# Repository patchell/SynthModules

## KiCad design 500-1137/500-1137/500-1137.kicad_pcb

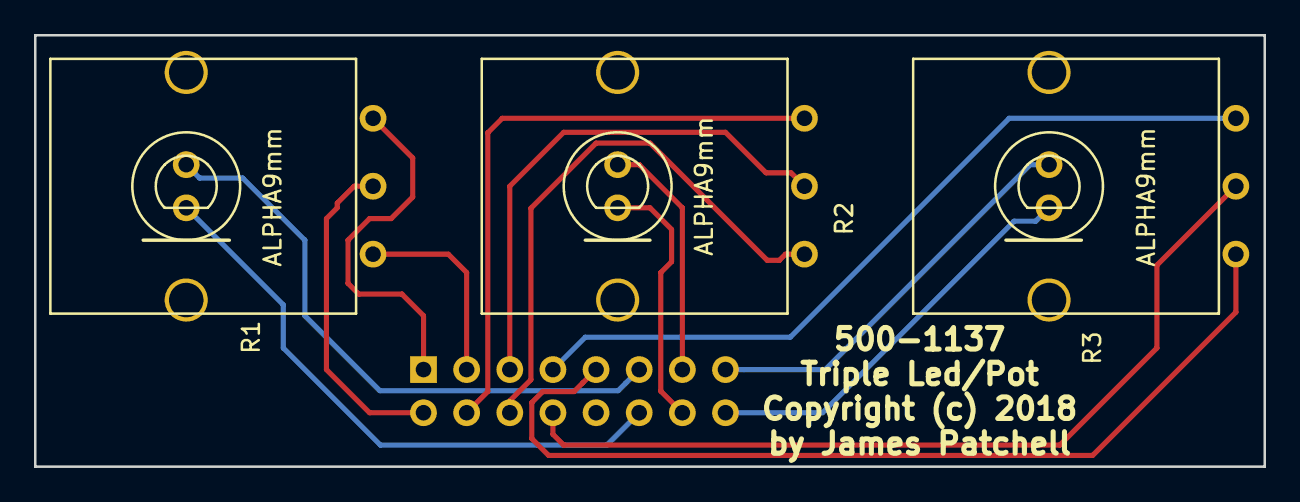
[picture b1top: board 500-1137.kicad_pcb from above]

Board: 2 copper layers, 72.4 x 25.4 mm, 4 parts (1 on the bottom side), 15 nets.

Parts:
P1: 500-1137; IDC8x2_Vert
R1, R2, R3: ALPHA9mm; Alpha9mmPotWithLED

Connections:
unnamed: P1.1, R1.3
unnamed: P1.2, R1.2
unnamed: P1.3, R1.1
unnamed: P1.4, R2.3
unnamed: P1.5, R2.2
unnamed: P1.6, R2.1
unnamed: P1.7, R3.3
unnamed: P1.8, R3.2
unnamed: P1.9, R3.1
unnamed: P1.11, R1.5
unnamed: P1.12, R1.4
unnamed: P1.13, R2.5
unnamed: P1.14, R2.4
unnamed: P1.15, R3.5
unnamed: P1.16, R3.4

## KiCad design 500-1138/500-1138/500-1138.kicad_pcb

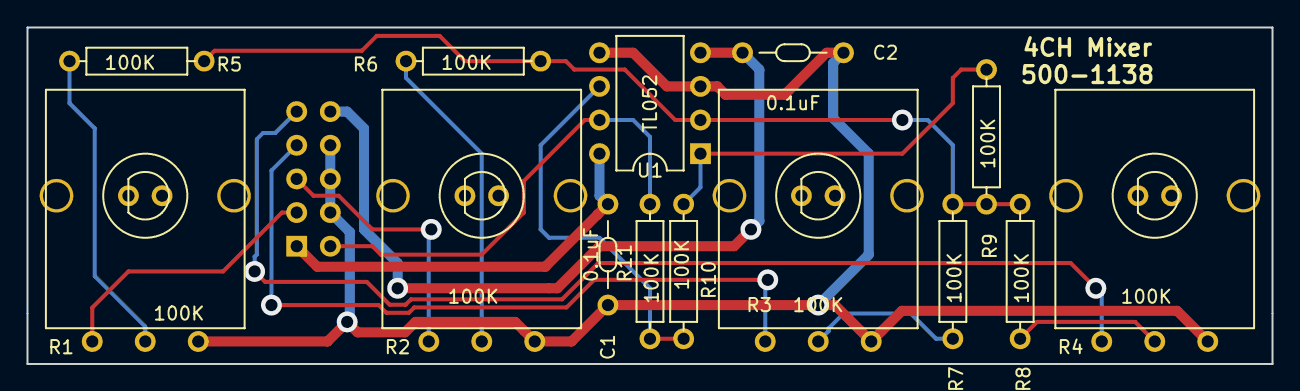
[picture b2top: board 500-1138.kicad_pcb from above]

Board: 2 copper layers, 94.0 x 25.4 mm, 15 parts (1 on the bottom side), 15 nets.

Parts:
C1, C2: 0.1uF; CAP-Bypass-0.3
P1: 500-1138; IDC5x2_Vert
R1, R2, R3, R4: 100K; Alpha9mmPotWithLED
R5, R6, R7, R8, R9, R10, R11: 100K; AXIAL0.4
U1: TL052; DIP8.3

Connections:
/V+: C1.1, P1.1, U1.8
/V-: C2.1, P1.10, U1.4
GND: C1.2, C2.2, P1.4, P1.6, P1.8, R1.3, R2.3, R3.3, R4.3, U1.3, U1.5
unnamed: P1.2, R11.2, U1.7
unnamed: P1.3, R1.1
unnamed: P1.5, R2.1
unnamed: P1.7, R3.1
unnamed: P1.9, R4.1
unnamed: R1.2, R5.1
unnamed: R2.2, R6.1
unnamed: R3.2, R7.1
unnamed: R4.2, R8.1
unnamed: R5.2, R6.2, R7.2, R8.2, R9.1, U1.2
unnamed: R9.2, R10.1, U1.1
unnamed: R10.2, R11.1, U1.6

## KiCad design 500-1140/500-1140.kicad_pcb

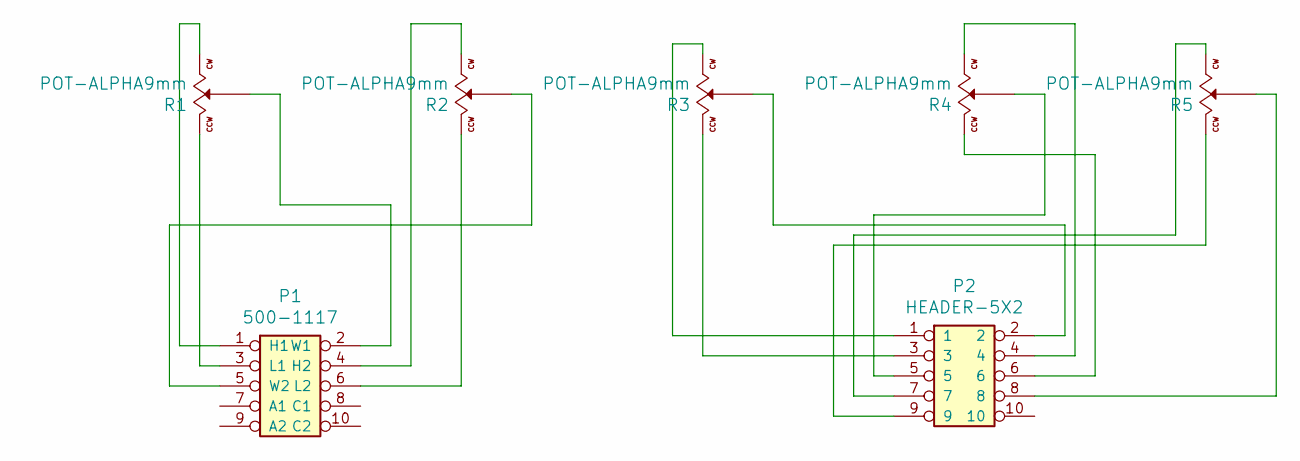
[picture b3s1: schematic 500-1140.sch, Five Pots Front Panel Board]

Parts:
P1: 500-1117; IDC5x2_Vert
P2: HEADER-5X2; IDC5x2_Vert
R1, R2, R3, R4, R5: POT-ALPHA9mm; Alpha_9mm_Pot

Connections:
unnamed: P1.1 (H1), R1.3 (B)
unnamed: P1.2 (W1), R1.2 (Wiper)
unnamed: P1.3 (L1), R1.1 (A)
unnamed: P1.4 (H2), R2.3 (B)
unnamed: P1.5 (W2), R2.2 (Wiper)
unnamed: P1.6 (L2), R2.1 (A)
unnamed: P2.1, R3.3 (B)
unnamed: P2.2, R3.2 (Wiper)
unnamed: P2.3, R3.1 (A)
unnamed: P2.4, R4.3 (B)
unnamed: P2.5, R4.2 (Wiper)
unnamed: P2.6, R4.1 (A)
unnamed: P2.7, R5.3 (B)
unnamed: P2.8, R5.2 (Wiper)
unnamed: P2.9, R5.1 (A)

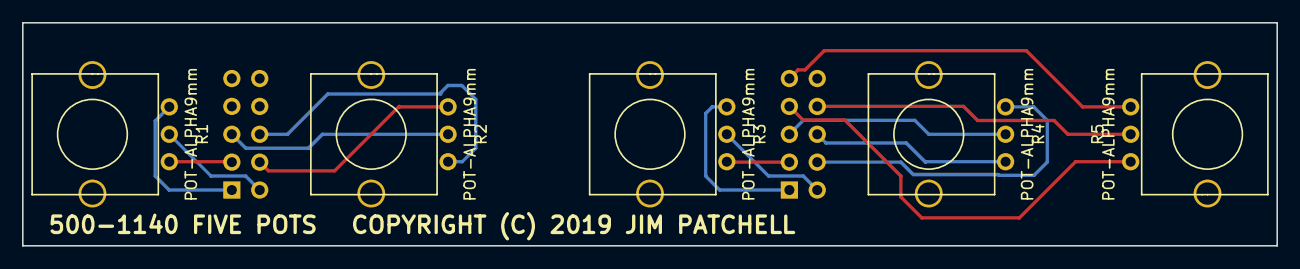
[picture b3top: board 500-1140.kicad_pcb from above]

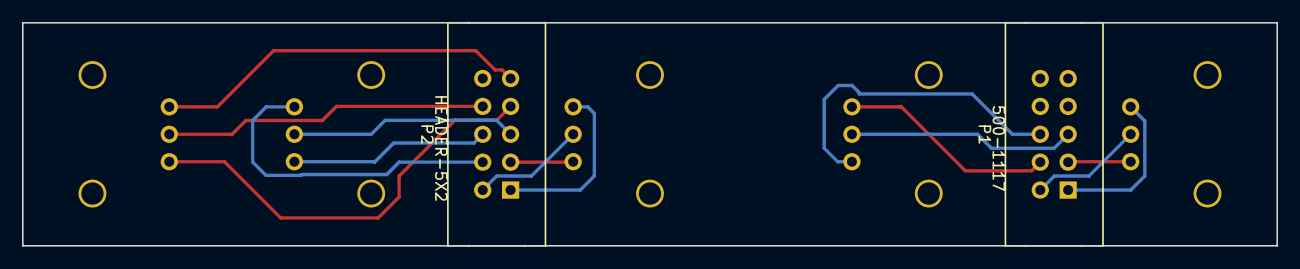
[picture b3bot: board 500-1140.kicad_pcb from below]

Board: 2 copper layers, 114.3 x 20.3 mm, 7 parts (2 on the bottom side), 15 nets.

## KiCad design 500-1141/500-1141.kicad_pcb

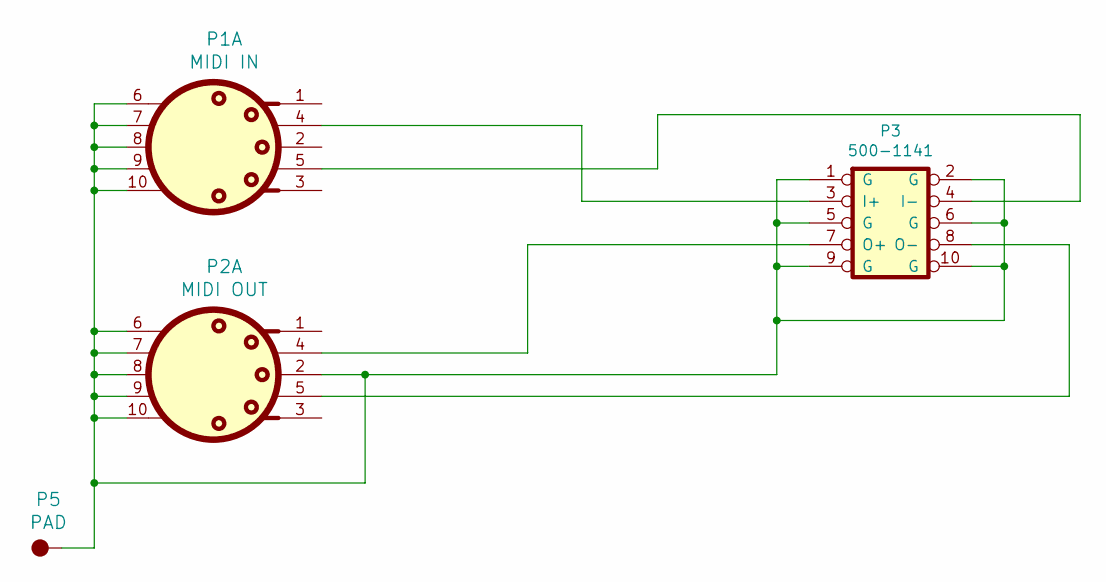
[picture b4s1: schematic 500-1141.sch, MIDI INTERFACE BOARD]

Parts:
P1: MIDI IN; DIN-5-PIN
P2: MIDI OUT; DIN-5-PIN
P3: 500-1141; IDC5x2_Vert
P5: PAD; MountingHole_125

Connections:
unnamed: P1.4, P3.3 (I+)
unnamed: P1.5, P3.4 (I-)
unnamed: P1.6, P1.7, P1.8, P1.9, P1.10, P2.2, P2.6, P2.7, P2.8, P2.9, P2.10, P3.1 (G), P3.2 (G), P3.5 (G), P3.6 (G), P3.9 (G), P3.10 (G), P5.1
unnamed: P2.4, P3.7 (O+)
unnamed: P2.5, P3.8 (O-)

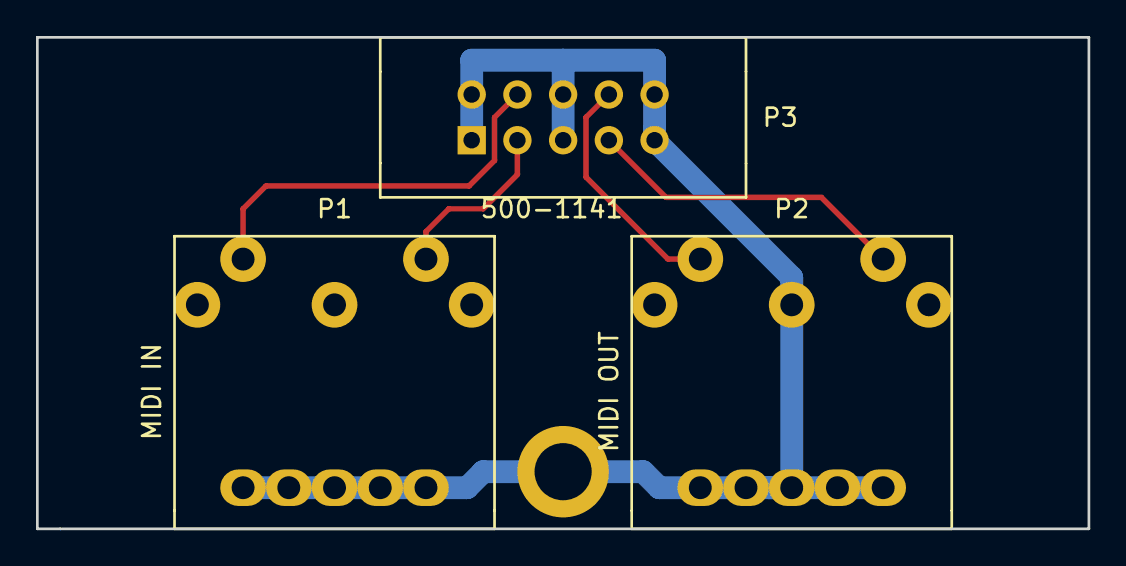
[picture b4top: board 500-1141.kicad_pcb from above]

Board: 2 copper layers, 58.4 x 27.3 mm, 4 parts (0 on the bottom side), 5 nets.

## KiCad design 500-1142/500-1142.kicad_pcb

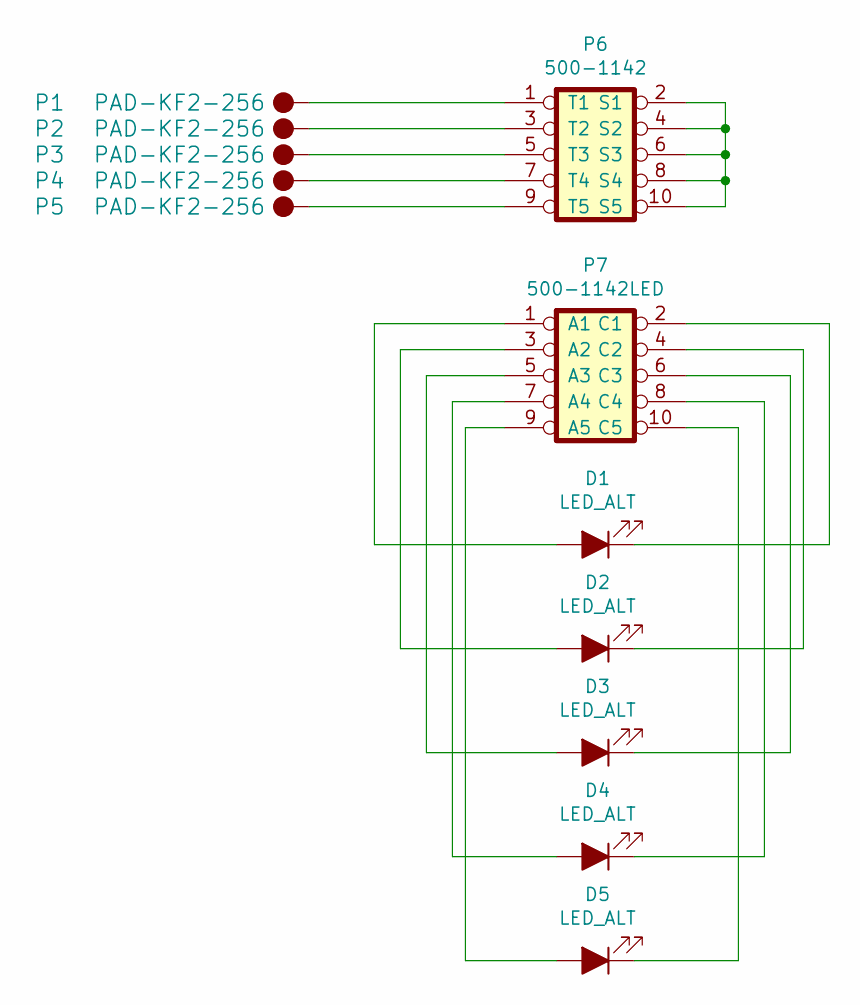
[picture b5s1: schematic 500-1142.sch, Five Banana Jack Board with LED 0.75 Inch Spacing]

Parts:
D1, D2, D3, D4, D5: LED_ALT; LED_5.0mm
P1, P2, P3, P4, P5: PAD-KF2-256; KF2-256-TerminalPad
P6: 500-1142; IDC5x2_Vert
P7: 500-1142LED; IDC5x2_Vert

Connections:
unnamed: D1.1 (K), P7.2 (C1)
unnamed: D1.2 (A), P7.1 (A1)
unnamed: D2.1 (K), P7.4 (C2)
unnamed: D2.2 (A), P7.3 (A2)
unnamed: D3.1 (K), P7.6 (C3)
unnamed: D3.2 (A), P7.5 (A3)
unnamed: D4.1 (K), P7.8 (C4)
unnamed: D4.2 (A), P7.7 (A4)
unnamed: D5.1 (K), P7.10 (C5)
unnamed: D5.2 (A), P7.9 (A5)
unnamed: P1.1, P6.1 (T1)
unnamed: P2.1, P6.3 (T2)
unnamed: P3.1, P6.5 (T3)
unnamed: P4.1, P6.7 (T4)
unnamed: P5.1, P6.9 (T5)
unnamed: P6.2 (S1), P6.4 (S2), P6.6 (S3), P6.8 (S4), P6.10 (S5)

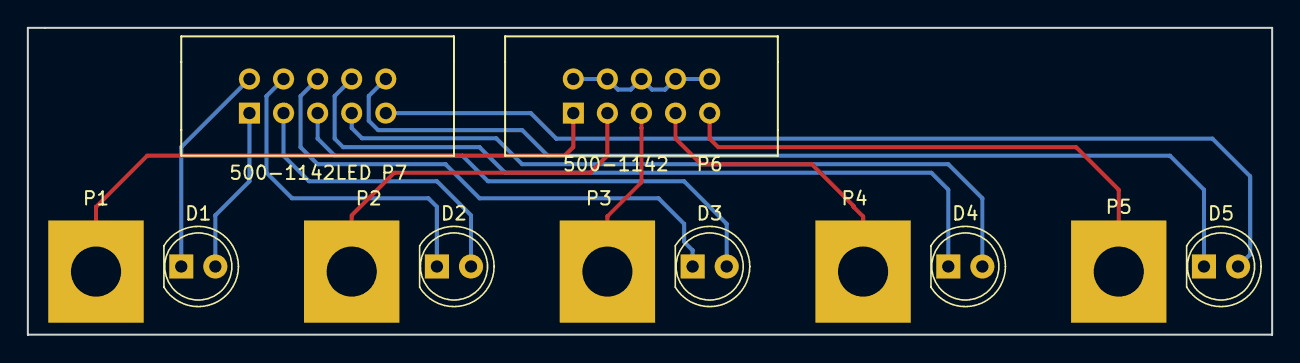
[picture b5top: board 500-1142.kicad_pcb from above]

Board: 2 copper layers, 92.7 x 22.9 mm, 12 parts (0 on the bottom side), 16 nets.

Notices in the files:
500-1137/500-1137/500-1137.kicad_pcb:
Copyright (c) 2018
500-1140/500-1140.kicad_pcb:
COPYRIGHT (C) 2019 JIM PATCHELL
